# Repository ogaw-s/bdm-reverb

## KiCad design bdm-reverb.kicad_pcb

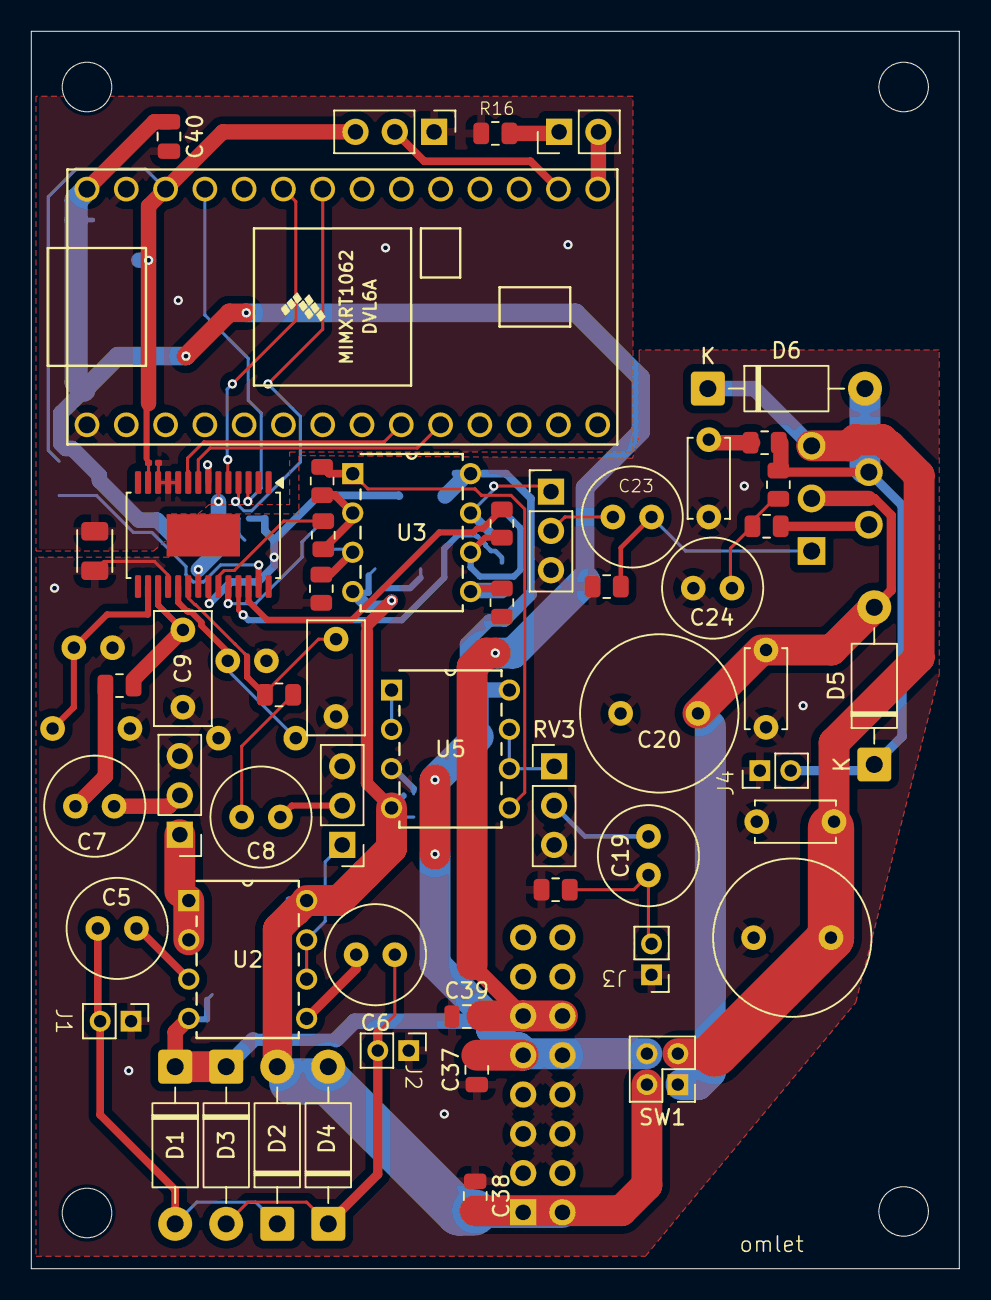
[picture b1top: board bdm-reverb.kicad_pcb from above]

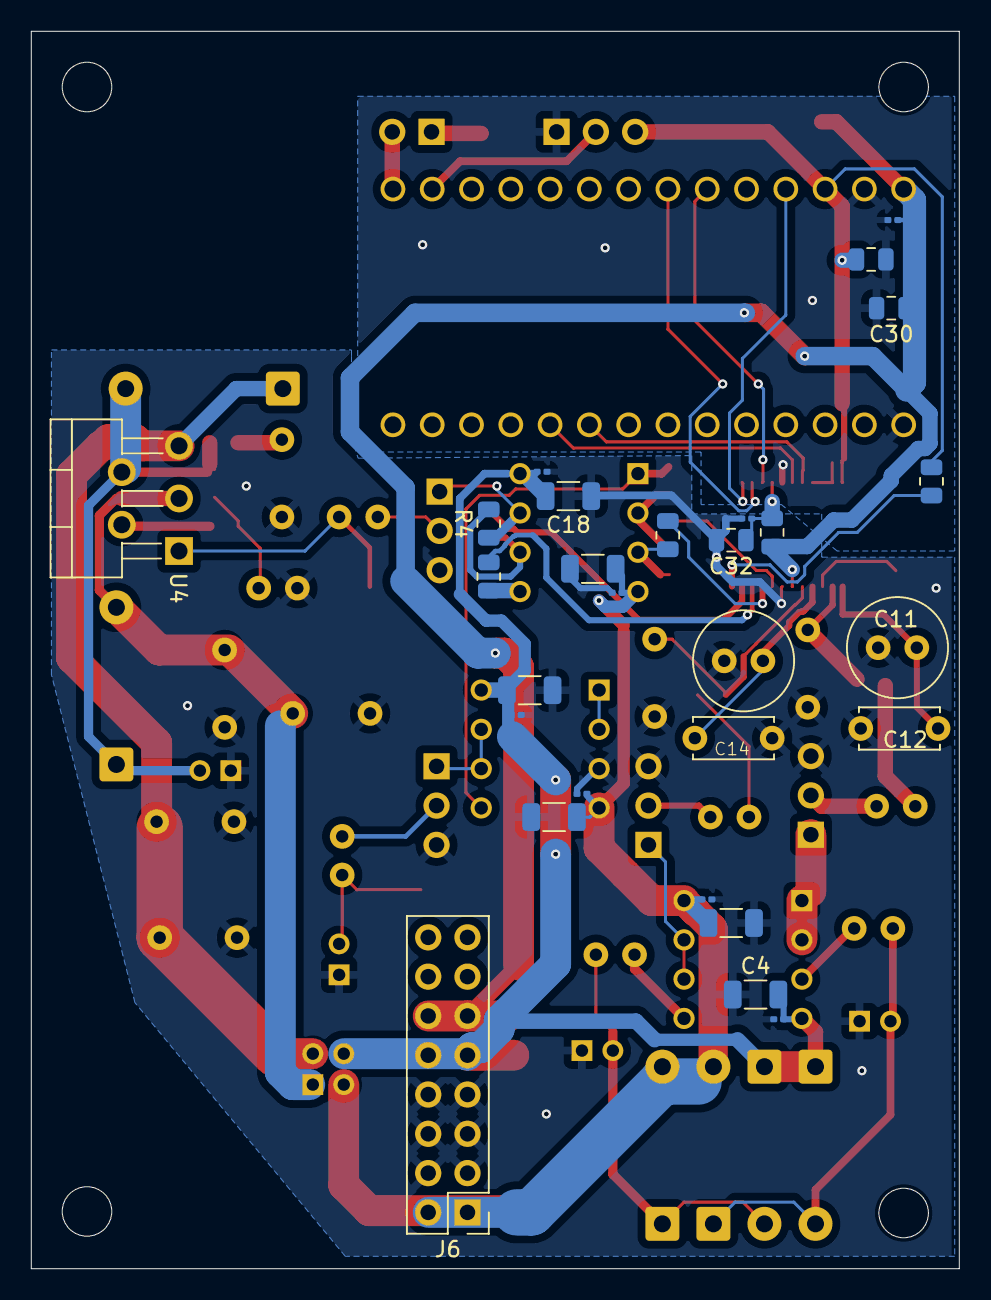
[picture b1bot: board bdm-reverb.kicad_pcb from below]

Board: 2 copper layers, 60.0 x 80.0 mm, 83 parts (28 on the bottom side), 52 nets.

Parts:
C1, C3, C15, C16, C27, C29, C31, C33, C34: 0.1u; C_0201_0603Metric
C2, C4, C17, C18, C35, C36: 10u; C_1206_3216Metric
C5, C6, C23: 1u; C_Radial_D6.3mm_H11.0mm_P2.50mm
C7, C8, C19: 10u; C_Radial_D6.3mm_H11.0mm_P2.50mm
C9, C10: 2.2n; C_Rect_L7.2mm_W3.5mm_P5.00mm_FKS2_FKP2_MKS2_MKP2
C11, C13: 4.7u; C_Radial_D6.3mm_H11.0mm_P2.50mm
C12, C14, C22, C25: 0.1u; C_Disc_D5.0mm_W2.5mm_P5.00mm
C20: 100u; C_Radial_D10.0mm_H20.0mm_P5.00mm
C21: 220u; C_Radial_D10.0mm_H20.0mm_P5.00mm
C24: 22u; C_Radial_D6.3mm_H11.0mm_P2.50mm
C26: 0.22u; C_Disc_D5.0mm_W2.5mm_P5.00mm
C28, C30, C32, C37, C38, C39, C40: 1u; C_0805_2012Metric
D1, D2, D3, D4: 1N5819; D_DO-41_SOD81_P10.16mm_Horizontal
D5, D6: 1N4007; D_DO-41_SOD81_P10.16mm_Horizontal
D7: LED; PinHeader_1x02_P2.54mm_Vertical
FB1: FerriteBead; L_Walsin_WLFM252009x
J1: input jack (line); simplejackwithpinheader
J2: input jack (piezo); simplejackwithpinheader
J3: output jack (line); simplejackwithpinheader
J4: output jack (spk); simplejackwithpinheader
J6: Conn_02x08_Odd_Even; PinHeader_2x08_P2.54mm_Vertical
R1, R2: 150; R_0805_2012Metric
R3, R4, R5, R6, R7, R8, R9, R10, R17: 10k; R_0805_2012Metric
R11: 100k; R_0805_2012Metric
R12: 22k; R_0805_2012Metric
R13: 680; R_0805_2012Metric
R14: 1; R_0805_2012Metric
R15: 13k; R_0805_2012Metric
R16: 5k; R_0805_2012Metric
R18: 2; R_0805_2012Metric
RV1, RV2, RV3, RV4, RV5: R_Potentiometer; PinHeader_1x03_P2.54mm_Vertical
SW1: SW_DPST; PinHeader_2x02_P2.00mm_Vertical
U1: Teensy4.0; Teensy40
U2, U3, U5: TL072
U4: TDA2030; TO-220-5_P3.4x3.7mm_StaggerOdd_Lead3.8mm_Vertical
VM4220M1: V4220M

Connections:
+5V: C29.1, C30.1, C39.2, C40.1, J6.11, J6.12, R18.1, U1.33 (VIN), VM4220M1.21 (VA)
+12V: C3.2, C4.2, C16.2, C18.2, C33.1, C35.1, C37.2, D1.1 (K), D3.1 (K), J6.9, J6.10, SW1.4, U2.4 (V-), U3.8 (V+), U5.8 (V+)
-12V: C1.1, C2.1, C15.1, C17.1, C34.2, C36.2, C38.2, D2.2 (A), D4.2 (A), J6.1, J6.2, SW1.2, U2.8 (V+), U3.4 (V-), U5.4 (V-)
GND1: C1.2, C2.2, C3.1, C4.1, C9.2, C10.2, C11.2, C12.2, C13.2, C14.2, C15.2, C16.1, C17.2, C18.1, C20.2, C21.2, C22.2, C24.2, C25.2, C26.2, C31.2, C32.2, C33.2, C34.1, C35.2, C36.1, C37.1, C38.1, C39.1, FB1.1, J1.S, J2.S, J3.S, J4.S, J6.3, J6.4, J6.5, J6.6, J6.7, J6.8, R5.1, R6.1, R11.1, R12.2, RV1.3, RV2.3, RV3.3, RV4.3, U5.3 (+), VM4220M1.18 (DEM1), VM4220M1.22 (AGND)
GND2: C27.2, C28.2, C29.2, C30.2, C40.2, FB1.2, R16.1, RV5.1, U1.1 (GND), U1.32 (GND), VM4220M1.7 (DGND), VM4220M1.10 (DIF1), VM4220M1.11 (DIF0), VM4220M1.12 (DEM0)
unnamed: C7.1, RV1.2
unnamed: C7.2, R1.1
unnamed: C8.1, RV2.2
unnamed: C8.2, R2.1
unnamed: C19.1, J3.T, R11.2
unnamed: C19.2, RV3.2
unnamed: C23.2, RV4.2
unnamed: C24.1, R13.2, R15.1
unnamed: C26.1, R14.2
unnamed: C5.1, D1.2 (A), D2.1 (K), J1.T
unnamed: C6.1, D3.2 (A), D4.1 (K), J2.T
unnamed: C20.1, C22.1, D5.2 (A), SW1.1, U4.3 (-Vs)
unnamed: D5.1 (K), D6.2 (A), J4.T, R14.1, R15.2, U4.4
unnamed: C21.1, C25.1, D6.1 (K), SW1.3, U4.5 (+Vs)
unnamed: D7.2 (A), U1.20 (13_SCK_CRX1_LED)
unnamed: D7.1 (K), R16.2
unnamed: R4.1, RV4.1, U3.7
unnamed: U1.9 (7_RX2_OUT1A), VM4220M1.9 (DIN)
unnamed: U1.10 (8_TX2_IN1), VM4220M1.8 (DOUT)
unnamed: RV5.2, U1.21 (14_A0_TX3_SPDIF_OUT)
unnamed: U1.27 (20_A6_TX5_LRCLK1), VM4220M1.4 (LRCK)
unnamed: U1.28 (21_A7_RX5_BCLK1), VM4220M1.5 (SLCK)
unnamed: U1.30 (23_A9_CRX1_MCLK1), VM4220M1.3 (XTI)
unnamed: C5.2, U2.3 (+)
unnamed: RV1.1, U2.1, U2.2 (-)
unnamed: C6.2, U2.5 (+)
unnamed: RV2.1, U2.6 (-), U2.7
unnamed: R6.2, R8.2, U3.3 (+)
unnamed: R3.2, R10.1, U3.2 (-)
unnamed: R5.2, R9.2, U3.5 (+)
unnamed: R4.2, R7.1, U3.6 (-)
unnamed: C23.1, R12.1, U4.1 (+)
unnamed: R13.1, U4.2 (-)
unnamed: U5.1, U5.2 (-)
unnamed: R3.1, U3.1, U5.5 (+)
unnamed: RV3.1, U5.6 (-), U5.7
unnamed: C10.1, R2.2, VM4220M1.20 (LIN+)
unnamed: C13.1, C14.1, VM4220M1.19 (LIN-)
unnamed: R9.1, VM4220M1.25 (LOUT+)
unnamed: R7.2, VM4220M1.26 (LOUT-)
unnamed: C9.1, R1.2, VM4220M1.17 (RIN+)
unnamed: C11.1, C12.1, VM4220M1.16 (RIN-)
unnamed: R8.1, VM4220M1.24 (ROUT+)
unnamed: R10.2, VM4220M1.23 (ROUT-)
unnamed: R17.2, VM4220M1.27 (RSTN)
unnamed: C31.1, C32.1, R18.2, VM4220M1.6 (VD)
unnamed: C27.1, C28.1, R17.1, RV5.3, U1.31 (3V3), VM4220M1.13 (VL)

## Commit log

2025-12-26 iroiro
